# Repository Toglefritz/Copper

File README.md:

# Copper

**Copper** is a web application built in Flutter that helps engineers analyze and improve their KiCad PCB designs. By parsing PCB design files, the application extracts key design information and uses Azure AI Services to provide insights, detect errors, and suggest optimizations.

## Features
- 📁 **Upload and Parse KiCad PCB Files** – Extracts design details from PCB design files (currently .kicad_pcb) files.
- 🔍 **Trace & Routing Analysis** – Evaluates trace widths, clearance, and routing efficiency.
- ⚡ **Power & Signal Integrity Insights** – Detects potential issues in power distribution and signal paths.
- 📊 **Manufacturability Review** – Ensures the PCB design meets fabrication constraints.
- 🤖 **AI-Powered Feedback** – Uses Azure AI Services for advanced analysis and recommendations.
- 📄 **Detailed Reports** – Generates structured feedback for engineers to refine their designs.

## Technology Stack

### Frontend:
- **Flutter Web** – Provides a responsive UI for analyzing PCB designs.
- **Dart** – Powers the application logic and interactions.

### Backend & AI Services:
- **Azure AI Services** – Performs AI-driven analysis on PCB design data.
- **Azure Functions** – Handles backend processing for file parsing and AI requests.
- **Azure Blob Storage** – Stores uploaded .kicad_pcb files and processed reports.

## Project Workflow

1️⃣ **User Uploads a KiCad PCB File**
The user selects a PCB design file (`.kicad_pcb`) file and uploads it to the application.

2️⃣ **Parsing the PCB File**
The application extracts key data from the file, including:

- Components & Footprints
- Traces, Vias & Copper Zones
- Netlists & Layer Information
- Design Rules & Constraints

This parsed data is stored in an internal representation that allows for structured analysis.

3️⃣ **AI-Powered Analysis with Azure AI Services**
Once the design data is structured, the application sends relevant information to Azure AI Services for further analysis. These services provide:

✅ Design Rule & Electrical Rule Compliance
- Identifies DRC & ERC violations using AI-assisted pattern recognition.
- Suggests potential fixes based on best practices.

✅ Trace & Routing Evaluation
- Detects bottlenecks, excessive via use, or unnecessary trace complexity.
- Provides insights into trace width adequacy for expected current loads.

✅ Power & Signal Integrity Analysis
- Checks ground planes, power distribution efficiency, and potential EMI issues.
- Suggests improvements for high-speed signal routing and differential pairs.

✅ Manufacturability & Assembly Review
- Uses AI to detect potential fabrication issues (e.g., silkscreen misalignment, solder mask clearance).
- Ensures the design aligns with common PCB manufacturing constraints.

4️⃣ **Generating a Report**
The application compiles the analysis results into a detailed report with:

- Issue Summaries & Severity Ratings
- Recommendations & Fixes
- Visual Annotations (where applicable)

5️⃣ **User Review & Iteration**
The user reviews the findings and applies necessary changes to their design in KiCad.

## Installation & Development

### Prerequisites:
- Flutter (latest stable version)
- Azure Account with AI Services configured

### Setup Instructions:

1. **Clone the repository**:

```sh
git clone https://github.com/Toglefritz/Circuit-Check
cd circuit-check
```

2. **Install dependencies**:

```sh
flutter pub get
flutter gen-l10n
```

3. **Set up environment variables for Azure services**:
// TODO: Document setup for Azure functions

4. **Run the application**:

```sh
flutter run -d chrome
```

## Roadmap & Future Enhancements

🚀 Upcoming Features:
- **Automated Fix Suggestions** – Apply design fixes directly from Copper.
- **Real-Time KiCad Plugin** – Direct integration with KiCad for instant feedback.
- **Custom Rule Configuration** – Allow users to define custom DRC/ERC checks.

## Contributing
Contributions to this project are welcomed and greatly appreciated!

1. Fork the repository
2. Create a feature branch (`feature-new-analysis`)
3. Commit your changes
4. Submit a pull request

## License
This project is licensed under the MIT License. See *LICENSE* for details.

## Disclaimer
In the creation of this application, artificial intelligence (AI) tools have been utilized. These tools have assisted in various stages of the plugin's development, from initial code generation to the optimization of algorithms.

It is emphasized that the AI's contributions have been thoroughly overseen. Each segment of AI-assisted code has undergone meticulous scrutiny to ensure adherence to high standards of quality, reliability, and performance. This scrutiny was conducted by the sole developer responsible for the app's creation.

Rigorous testing has been applied to all AI-suggested outputs, encompassing a wide array of conditions and use cases. Modifications have been implemented where necessary, ensuring that the AI's contributions are well-suited to the specific requirements and limitations inherent in the technologies related to this app's functionality.

Commitment to the apps's accuracy and functionality is paramount, and feedback or issue reports from users are invited to facilitate continuous improvement.

It is to be understood that this app, like all software, is subject to evolution over time. The developer is dedicated to its progressive refinement and is actively working to surpass the expectations of the community.

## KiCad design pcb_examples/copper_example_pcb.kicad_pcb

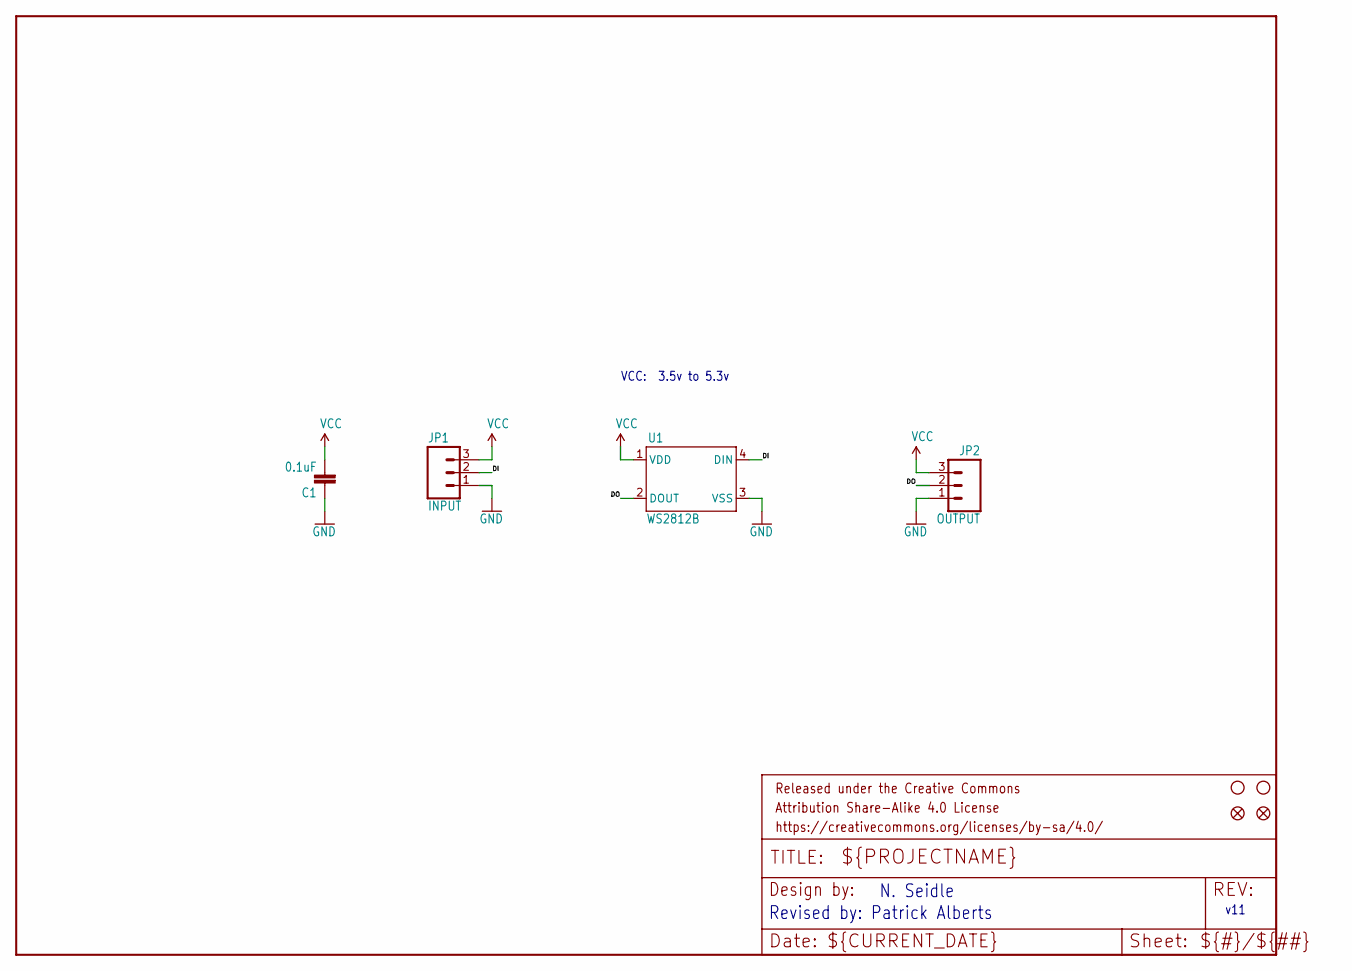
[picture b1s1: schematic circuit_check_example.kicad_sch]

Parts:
C1: 0.1uF; 0603-CAP
FID1, FID2: FIDUCIAL1X2; FIDUCIAL-1X2
FRAME1: FRAME-LETTER; CREATIVE_COMMONS
JP1: INPUT; 1X03
JP2: OUTPUT; 1X03
JP4, JP15: STAND-OFF
U1: WS2812B

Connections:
DI: JP1.2, U1.4 (DIN)
DO: JP2.2, U1.2 (DOUT)
GND: C1.1, JP1.1, JP2.1, U1.3 (VSS)
VCC: C1.2, JP1.3, JP2.3, U1.1 (VDD)

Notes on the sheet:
VCC: 3.5v to 5.3v
Revised by: Patrick Alberts
v11
N. Seidle

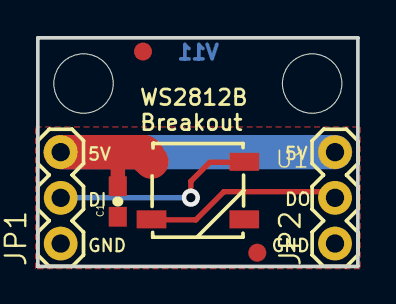
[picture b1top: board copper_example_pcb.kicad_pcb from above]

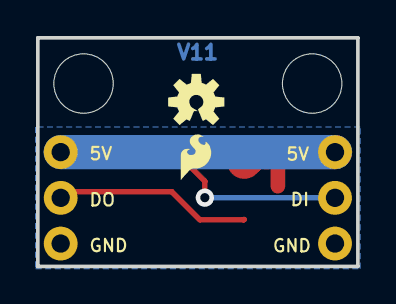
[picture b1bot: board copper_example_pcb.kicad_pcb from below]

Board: 2 copper layers, 17.8 x 12.7 mm, 11 parts (2 on the bottom side), 4 nets.

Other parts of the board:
LOGO1: OSHW-LOGOS; OSHW-LOGO-S
LOGO2: SFE_LOGO_FLAME.1_INCH; SFE_LOGO_FLAME_.1

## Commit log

2025-02-22 initialize Flutter project with essential files and configurations :zap:
2025-02-22 Created README :scroll:
2025-02-22 Created base app architecture from Flutter template :building_construction:
2025-02-22 Added ability to provide app with PCB files :page_facing_up:
2025-02-22 Added AppBar :tropical_fish:
2025-02-23 Created KiCAD 9.x PCB file parser :t-rex:
2025-02-23 Created analysis route :alembic:
2025-02-24 Added component connection schematic widget :spider_web:
2025-02-25 Updated app branding :art:
2025-02-25 Reorganized project to include Azure functions :elephant:
2025-02-25 Updated documentation :book:
2025-02-25 Updated GitHub Actions config :shower:
2025-02-25 Created GitHub Actions pipeline :shower:
2025-02-26 Created Azure Function App for getting AI completion :brain:
2025-03-03 Added authentication system 🚪
2025-03-04 Persist authentication state between sessions 🕔
2025-03-07 Added description input to design overview :pencil:
2025-03-07 Updated project description field 🐄
2025-03-07 Refactored design overview route :black_joker:
2025-03-08 Updated GitHub Actions config :octopus:
2025-03-08 Added a logout button 👋
2025-03-08 Added PCB analysis service 🚀
2025-03-08 Code cleanup :soap:
2025-03-09 Updated prompt content construction :speech_balloon:
2025-03-09 Updated GitHub Actions config :clapper:
2025-03-09 Added loader while analyzing PCB :hourglass:
2025-03-10 Created display for prompt results :fish:
2025-03-14 Created functions for Cosmos CRUD operations :nut_and_bolt:
2025-03-14 Added function for getting all user designs :hot_pepper:
2025-03-15 Updated documentation 📜
2025-03-18 Save PCB design to cloud after parsing ☁️
2025-03-18 Save PCB design description to cloud :partly_sunny:
2025-03-18 Added home navigation to logo 🏠
2025-03-21 Get PCB designs from Cosmos DB 👾
2025-03-22 Select from saved projects :floppy_disk:
2025-03-22 Added ability to delete PCB designs 🚫
2025-03-22 Ignore video in repo 📹
2025-03-22 Updated GitHub Actions 🎬
2025-03-22 Renamed example PCB ⚡

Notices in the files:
pcb_examples/circuit_check_example.kicad_sch:
Released under the Creative Commons
https://creativecommons.org/licenses/by-sa/4.0
parts and their libraries:
Released under the Creative Commons Attribution Share-Alike 4.0 License
